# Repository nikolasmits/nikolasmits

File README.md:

<h1>Hi, I'm Nikolaos! <br/><a href="https://www.linkedin.com/in/nikolas-mitsokapas-6b18a51ba/">Electronic and Electrical Engineer</a>, <a href="https://www.linkedin.com/in/nikolas-mitsokapas-6b18a51ba/">Computer Science</a>

<h2>🤖 Control Systems and Robotics:</h2>

- <b>Automated Component Embedding Integration for an FDM 3D Printer</b>
  - [Modifying a TAZ 5 3D Printer with an end-effector gripper, toolchange mechanism & machine vision](https://github.com/nikolasmits/nikolasmits/tree/main/automated-component-embedding-integration-for-an-fdm-3d-printer)
- <b>Designing and Testing a a Maze Solving Robot</b>
  - [Four-wheeled robot with sensing and actuation for obstacle-based movement](https://github.com/nikolasmits/nikolasmits/tree/main/maze-solving-robot)
- <b>Braille-to-text-to-speech reading robot</b>
  - [UCL Neuphonic AI Hackathon](https://github.com/nikolasmits/nikolasmits/tree/main/braille-reading-robot)
- <b>Pick-and-place (PnP) Robot</b>
  - [Forward Kinematics, Inverse Kinematics & Trajectory planning of a PnP Robot](https://github.com/nikolasmits/nikolasmits/tree/main/pnp_robot)
- <b>Connected Bioreactor Control System</b>
  - [Remote monitoring and control of a small-scale bioreactor](https://github.com/nikolasmits/nikolasmits/tree/main/bioreactor-control-system)
- <b>Robotic Surgical Tool Design</b>
  - [Conformal tool design, surgical planning](https://github.com/nikolasmits/nikolasmits/tree/main/bioreactor-control-system)

<h2>👨‍💻 ML & DL Projects:</h2>

- <b>Sentiment Analysis (Deep Learning & Natural Language Processes)</b>
  - [Logistic Regression, Word2vec, LSTM & DistilBERT models](https://github.com/nikolasmits/nikolasmits/tree/main/sentiment-analysis)
- <b>Backpropagation in MLP, Transfer Learning in CNN and RL</b>
  - [Regression, Classification, Transfer Learning and Q-Learning](https://github.com/nikolasmits/nikolasmits/tree/main/backprop-mlp-transfer-learning-cnn-rl)
- <b>Image Procession</b>
  - [MATLAB Design for Image Processing](https://github.com/nikolasmits/nikolasmits/tree/main/image-processing)
- <b>Industrial Automation</b>
  - [Automated System for Deburring, Polishing and Storing car rims](https://github.com/nikolasmits/nikolasmits/tree/main/industrial-automation)

<h2> 🔌 Circuit Design and Hardware Development:</h2>

- <b>Smart Gym Wearable (Advanced Embedded Design for IoTSystems)</b>
  - [Embedded Systems, Schematic & PCB Design](https://github.com/nikolasmits/nikolasmits/tree/main/smart-gym-wearable)
- <b>Bio-signal Based Human Machine Interface (sEMG)</b>
  - [Schematic, PCB Design & Fabrication of an sEMG](https://github.com/nikolasmits/nikolasmits/tree/main/semg)
- <b>Digital Power Supply</b>
  - [Design & Fabrication of a DPS subsystem](https://github.com/nikolasmits/nikolasmits/tree/main/dps)

<h2> 🧠 Digital Design and Computer Architecture:</h2>

- <b>Design of a RISC-V central CPU</b>
  - [SystemVerilog description and Icarus Verilog simulation](https://github.com/nikolasmits/nikolasmits/tree/main/risc-v-central-cpu)
- <b>Audio descrambler</b>
  - [Design of digital audio descrambler](https://github.com/nikolasmits/nikolasmits/tree/main/audio-descrambler)

<h2> 📈 Simulation, Modelling and Technical Analysis:</h2>

- <b>Enhancement of Optical Absorption of Silicon Photovoltaics</b>
  - [Study of a hydrogenated amorphous silicion thin film PV cell with periodic gold nanowire gratings](https://github.com/nikolasmits/nikolasmits/tree/main/enhancement-of-optical-absorption-of-silicon-photovoltaics)
- <b>Digital transmitter, AWGN Communication channel & Digital Receiver</b>
  - [Design of a communication system](https://github.com/nikolasmits/nikolasmits/tree/main/comm-system)
- <b>Environmental Systems Mathematical Modelling</b>
  - [Simulating pollutant propagation across the Great Lakes](https://github.com/nikolasmits/nikolasmits/tree/main/environmental-systems-mathematical-modelling)
- <b>Mathematical model assessing the effects of altitude on the atmospheric pressure and density of air</b>
  - [MATLAB Mathematical model assessment](https://github.com/nikolasmits/nikolasmits/tree/main/mathematical-model-assessing-the-effects-of-altitude-on-the-atmospheric-pressure-and-density-of-air)
- <b>AIESEC Global Financial Case Competition</b>
  - [Financial performance and three-year projection](https://github.com/nikolasmits/nikolasmits/tree/main/aiesec-global-financial-case-competition)

<h2> 🤳 Connect with me:</h2>

[][linkedin]
[][email]

[email]: mailto:n.mitsokapas2003@gmail.com
[linkedin]: https://www.linkedin.com/in/nikolas-mitsokapas-6b18a51ba/

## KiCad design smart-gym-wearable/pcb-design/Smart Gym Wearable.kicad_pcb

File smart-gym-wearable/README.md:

# Smart Gym Wearable: Embedded Hardware and PCB Design

## Overview
This project involved the end-to-end hardware design of a **Smart Gym Wearable** intended to monitor workout motion and physiological state during exercise. The device combines:

- **motion sensing** using an ADXL343 3-axis accelerometer
- **heart-rate and pulse oximetry sensing** using the MAX30102
- **wireless communication** through an STM32WB55CEU6 with integrated Bluetooth Low Energy (BLE)
- **external flash memory** for extended data storage
- and a **battery-powered power management system** suitable for wearable use. 

The project covered the full hardware workflow from specification and component selection through schematic design, PCB layout, BOM preparation, and design-rule verification. :contentReference[oaicite:3]{index=3} :contentReference[oaicite:4]{index=4}

## Project Context
This project was completed for **ELEC0152: Advanced Embedded Design for IoT Systems – Circuit Design and Implementation**. The coursework required an academic-style hardware design report documenting the complete process of designing and implementing an electronic system, including:

- circuit specification
- refined component selection
- system block diagram
- full schematic
- PCB design
- and bill of materials analysis. :contentReference[oaicite:5]{index=5}

The workshop guidance also required:
- at least one sensor using **SPI, I2C, or UART**
- at least one actuator
- at least two protocols among **SPI, I2C, UART**
- **USB power and data**
- and **wireless communication**. :contentReference[oaicite:6]{index=6}

This wearable satisfies those requirements through:
- sensor interfacing over **I2C**
- external memory over **QSPI/SPI**
- USB connectivity
- BLE wireless communication
- and LED-based user feedback. :contentReference[oaicite:7]{index=7}

## My Contribution
This project appears to be an individual hardware design project, and the uploaded report is written in first person around your own design decisions. The work demonstrates my ability to take a product idea from system requirements to a manufacturable PCB implementation.

My contribution included:
- defining the wearable’s hardware objectives
- selecting and justifying the major ICs and support circuitry
- designing the full schematic
- creating the PCB layout in KiCad
- setting design rules and checking manufacturability
- compiling the BOM and supplier-linked part list
- and documenting the design trade-offs in a formal hardware report. :contentReference[oaicite:8]{index=8}

## Product Motivation
The report frames the wearable around a real user problem: while commercial devices such as fitness trackers and smartwatches provide high-level metrics, they often provide limited feedback on **exercise execution quality**, **repetition consistency**, or **training efficiency**. The device was therefore designed to support structured resistance training by monitoring movement and physiological state while transmitting raw data to a smartphone for higher-level analysis. :contentReference[oaicite:9]{index=9}

This gives the project a strong product-engineering angle rather than being only a component-integration exercise.

## System Architecture
The wearable is built around the **STM32WB55CEU6**, which was selected as the central MCU/SoC because it combines:
- microcontroller capability
- low-power operation
- and integrated **Bluetooth Low Energy** support,

making it well suited for a compact wearable design. :contentReference[oaicite:10]{index=10}

The main subsystems shown across the report and schematics are:
- motion sensing
- optical biometric sensing
- mixed-voltage I2C interfacing
- external flash memory
- battery charging and regulation
- USB connection
- and user input/output. :contentReference[oaicite:11]{index=11}

## Motion Sensing: ADXL343 Accelerometer
The design uses the **ADXL343**, a 3-axis digital MEMS accelerometer. According to its datasheet, it supports:
- selectable ranges up to **±16 g**
- digital output over **SPI or I2C**
- motion-related features such as activity, inactivity, tap, double-tap, and free-fall detection
- and low-power operation down to **23 µA**. :contentReference[oaicite:12]{index=12}

This makes it a good fit for workout tracking, where the device needs to capture both static orientation and dynamic motion while remaining power-efficient.

Your accelerometer schematic shows:
- **3.3 V supply**
- local decoupling capacitors
- interrupt lines
- and pull-up resistors for the I2C bus,

which indicates correct attention to practical digital sensor integration rather than just symbolic connection. The uploaded noise-vs-output-data-rate figure also shows awareness of the trade-off between bandwidth and noise in motion sensing, which is particularly relevant in movement analysis for exercise tracking. :contentReference[oaicite:13]{index=13}

## Biometric Sensing: MAX30102 Pulse Oximeter and Heart-Rate Sensor
The wearable uses the **MAX30102** for optical heart-rate and blood-oxygen sensing. The datasheet describes it as an integrated pulse oximeter and heart-rate monitor module designed specifically for **wearable devices**, with:
- internal LEDs
- photodetectors
- ambient-light rejection
- FIFO support
- and low-power operation. It operates with a **1.8 V logic supply** and a separate **3.3 V LED supply**. :contentReference[oaicite:14]{index=14}

That voltage requirement directly explains one of the more interesting design decisions in your schematic: the use of a **voltage-level translator** between the MCU side and the sensor side.

## Mixed-Voltage I2C and Level Translation
Because the MAX30102 uses a lower logic supply than the main 3.3 V MCU domain, the design includes the **PCA9306** dual bidirectional I2C voltage-level translator. According to the datasheet, the PCA9306 is intended for bidirectional translation of I2C/SMBus signals across voltage domains without the need for a direction pin, while requiring pull-up resistors on both sides of the bus. 

Your schematic reflects this correctly by placing the translator between the sensor-side and main I2C-side buses, with supporting pull-ups and enable handling. This is a strong design choice because it shows awareness of:
- logic-level compatibility
- bus integrity
- and safe integration of mixed-voltage peripherals in a wearable system. 

## Memory Expansion: External Flash
The design also includes **external QSPI flash memory** (`W25Q128JVS`) connected through dedicated flash control and IO lines. This is a strong systems decision because it extends local storage for raw sensor data beyond what would be practical using only internal MCU memory. The report explicitly mentions this as part of the design rationale for capturing workout data before or alongside wireless transfer. :contentReference[oaicite:17]{index=17}

Including both BLE transmission and local memory support makes the system much more realistic as a wearable platform.

## Power Management and Battery Charging
A key strength of the project is its complete power subsystem. The design includes:
- a **lithium-ion battery**
- the **MCP73832** charge-management IC
- and the **MIC5365-3.3** LDO regulator. 

The MCP73832 datasheet and your schematic indicate a simple Li-ion charging solution with charge programming through a resistor, while the MIC5365 provides a regulated **3.3 V rail** with:
- low dropout
- low quiescent current
- and strong PSRR,
which is highly suitable for battery-powered portable electronics. :contentReference[oaicite:18]{index=18}

This is particularly important in a mixed-signal wearable, where clean regulation benefits both the MCU and noise-sensitive sensors.

## User Interaction and Feedback
The design includes:
- a **pushbutton** for starting and ending workouts
- and LED indicators for workout state / user feedback. 

This satisfies the actuator requirement from the workshop guidance and also improves usability by giving the user a simple physical interaction point rather than requiring all control through software alone. :contentReference[oaicite:19]{index=19}

## PCB Design
The PCB work is one of the strongest parts of this project. The uploaded board views show:
- a compact rectangular form factor
- routed top and bottom copper
- dense mixed-signal placement
- dedicated sensor areas
- and an RF/antenna-aware layout region. 

The report also states that the PCB design process considered:
- RF constraints for the BLE antenna path
- component placement constraints
- grounding
- routing strategy
- and manufacturability. :contentReference[oaicite:20]{index=20}

The antenna datasheet you uploaded also suggests explicit attention to PCB antenna footprint and layout recommendations, which is an important sign of real embedded-RF design awareness rather than treating BLE as just a software feature. :contentReference[oaicite:21]{index=21}

## BOM and Component Selection
The BOM screenshots and component list show that the project did not stop at schematic completion. It includes:
- actual manufacturer part numbers
- footprints
- supplier / assembly information
- and availability checks.

The report and coursework brief both emphasise performance, availability, and cost trade-offs in component selection, and your uploaded stock screenshots support that this was actively considered for parts such as:
- MAX30102
- MCP73832
- and MIC5365. 

That makes this much closer to a real hardware design project than a purely academic schematic.

## Verification and Manufacturability
The uploaded screenshots show:
- **ERC with zero violations**
- **DRC with zero violations**
- and explicit PCB constraint settings for clearance, track width, annular rings, vias, and board-edge rules.

This is a very important portfolio point because it demonstrates that the PCB was not only drawn, but checked against practical manufacturability and consistency rules. In other words, the project reflects a design flow aimed at real fabrication rather than only conceptual layout.

## Why This Project Matters
What makes this project strong is that it combines several engineering domains in one device:

- embedded hardware design
- mixed-voltage digital interfacing
- low-power wearable sensing
- biometric and motion sensor integration
- battery charging and regulation
- BLE-ready embedded platform design
- memory expansion
- PCB layout and manufacturability

This is the kind of project that shows genuine readiness for embedded hardware, IoT, wearable technology, and PCB/system design roles.

## Engineering Skills Demonstrated
This project demonstrates skills in:
- **embedded hardware architecture**
- **wearable device design**
- **PCB design in KiCad**
- **sensor integration over I2C**
- **mixed-voltage interface design**
- **power management and Li-ion charging**
- **regulator selection and low-power design**
- **external flash integration**
- **BLE-aware PCB design**
- **design-rule verification**
- **BOM preparation and sourcing**
- **technical hardware reporting in academic/professional style**. 

## What I Learned
This project strengthened my understanding of how a complete embedded wearable is developed from the ground up. In particular, it showed me how important it is to think across the full hardware stack: product requirements, component compatibility, supply domains, bus protocols, signal integrity, battery management, PCB layout, and manufacturability all interact. It also reinforced that good hardware design is not only about making a circuit function, but about making it robust, power-efficient, buildable, and appropriate for the real application. 

## Repository Contents
- `README.md` – project summary
- `report/` – final hardware design report
- `pcb-design/` – KiCad project files
- `schematics-design/` – key schematic screenshots
- `images/` – PCB views, BOM, ERC/DRC, and component screenshots
- `datasheets/` – supporting technical references

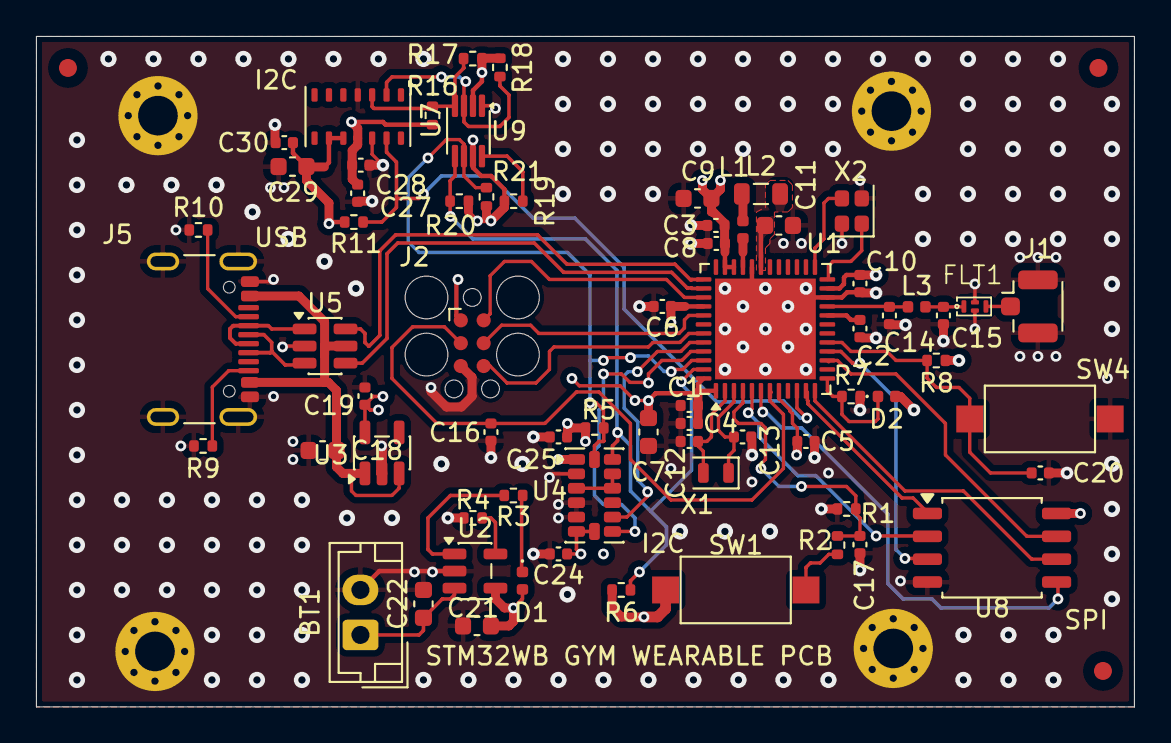
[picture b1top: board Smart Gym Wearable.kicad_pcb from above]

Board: 4 copper layers, 61.0 x 37.2 mm, 74 parts (0 on the bottom side), 47 nets.

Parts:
BT1: 4.2V; JST_EH_B2B-EH-A_1x02_P2.50mm_Vertical
C1, C2, C3, C4, C5, C6, C8, C10, C16, C17, C20: 100n; C_0402_1005Metric
C7, C9, C11, C18, C21, C22, C29: 4u7; C_0603_1608Metric
C12, C13: 10p; C_0402_1005Metric
C14: 0p8; C_0402_1005Metric
C15: 0p3; C_0402_1005Metric
C19: 4u7; C_0402_1005Metric
C24: 1u; C_0402_1005Metric
C25, C28, C30: 0u1; C_0402_1005Metric
C27: 10u; C_0402_1005Metric
D1, D2: LED; LED_0402_1005Metric
FID1, FID2, FID3: Fiducial; Fiducial_1mm_Mask2mm
FLT1: DLF162500LT-5028A1
H1, H2, H3, H4: MountingHole_Pad; MountingHole_2.2mm_M2_Pad_Via
J1: Conn_Coaxial; U.FL_Hirose_U.FL-R-SMT-1_Vertical
J2: TC2030; Tag-Connect_TC2030-IDC-FP_2x03_P1.27mm_Vertical
J5: USB_C_Receptacle_USB2.0_16P; USB_C_Receptacle_GCT_USB4105-xx-A_16P_TopMnt_Horizontal
L1: 10n; L_0402_1005Metric
L2: 10u; L_0805_2012Metric
L3: 2n7; L_0402_1005Metric
R1, R9, R10: 5k1; R_0402_1005Metric
R2: 100R; R_0402_1005Metric
R3, R7: 470R; R_0402_1005Metric
R4: 2k; R_0402_1005Metric
R5, R6: 4k7; R_0402_1005Metric
R8: 10k; R_0402_1005Metric
R11, R17, R18, R20, R21: 3k3; R_0402_1005Metric
R16: 1k; R_0402_1005Metric
R19: 200k; R_0402_1005Metric
SW1, SW4: SW_Push; SW_SPST_CK_RS282G05A3
U1: STM32WB55CEU6; QFN-48-1EP_7x7mm_P0.5mm_EP5.6x5.6mm
U2: MCP73832-2-OT; SOT-23-5
U3: MIC5365-3.3YD5; TSOT-23-5
U4: ADXL343; LGA-14_3x5mm_P0.8mm_LayoutBorder1x6y
U5: USBLC6-2SC6; SOT-23-6
U7: MAX30102; Maxim_OLGA-14_3.3x5.6mm_P0.8mm
U8: W25Q128JVS; SOIC-8_5.3x5.3mm_P1.27mm
U9: PCA9306DC1; VSSOP-8_2.3x2mm_P0.5mm
X1: 32kHz768; Crystal_SMD_2012-2Pin_2.0x1.2mm
X2: 32MHz; Crystal_SMD_2016-4Pin_2.0x1.6mm

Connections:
+1V8: C27.1, C28.1, R16.1, U7.11 (VDD)
+3.3V: C1.1, C2.1, C3.1, C4.1, C5.1, C6.1, C7.1, C8.1, C9.1, C10.1, C19.1, C24.1, C25.1, C29.1, C30.1, D2.2 (A), J2.1 (VCC), R5.1, R6.1, R8.2, R11.2, R17.2, R18.2, R19.2, R20.2, R21.2, SW1.2, U1.1 (VBAT), U1.8 (VDDA), U1.20 (VDD), U1.23 (VDDRF), U1.34 (VDDSMPS), U1.35 (VDD), U1.40 (VDDUSB), U1.48 (VDD), U3.5 (VOUT), U4.1 (Vdd_I/O), U4.6 (Vs), U4.7 (~CS), U7.9 (VLED+), U7.10 (VLED+), U8.8 (VCC), U9.2 (VREF1), U9.7 (VREF2)
+5V: C18.1, C21.1, D1.2 (A), J5.A4 (VBUS), J5.A9 (VBUS), J5.B4 (VBUS), J5.B9 (VBUS), U2.4 (V_{DD}), U3.1 (VIN), U3.3 (EN), U5.5 (VBUS)
/STM32 base circuit/BOOT0: C17.1, R1.1, R2.1, U1.4 (PH3)
/STM32 base circuit/HSE_IN: U1.25 (OSC_IN), X2.3
/STM32 base circuit/HSE_OUT: U1.24 (OSC_OUT), X2.1
/STM32 base circuit/LSE_IN: C12.1, U1.2 (PC14), X1.2
/STM32 base circuit/LSE_OUT: C13.1, U1.3 (PC15), X1.1
/STM32 base circuit/RF: C14.1, L3.1, U1.21 (RF1)
/STM32 base circuit/RF_ANT: FLT1.3 (OUT), J1.1 (In)
/STM32 base circuit/RF_MATCH: C15.1, FLT1.1 (IN), L3.2
/STM32 base circuit/SMPSFB: C11.1, L2.2, U1.31 (VFBSMPS)
/STM32 base circuit/SMPSLX: L1.1, U1.33 (VLXSMPS)
/STM32 base circuit/SMPSLXL: L1.2, L2.1
/STM32 base circuit/SWD_CLK: J2.4 (SWCLK), U1.41 (PA14)
/STM32 base circuit/SWD_DIO: J2.2 (SWDIO), U1.39 (PA13)
/STM32 base circuit/SWD_TRC: J2.6 (SWO), U1.43 (PB3)
/USB/USBC_D+: J5.A6 (D+), J5.B6 (D+), U5.3 (I/O2)
/USB/USBC_D-: J5.A7 (D-), J5.B7 (D-), U5.1 (I/O1)
/USB/USB_CC1: J5.A5 (CC1), R10.1
/USB/USB_CC2: J5.B5 (CC2), R9.1
FLASH_CLK: U1.12 (PA3), U8.6 (CLK)
FLASH_CS: U1.11 (PA2), U8.1 (~CS)
GND: BT1.2 (-), C1.2, C2.2, C3.2, C4.2, C5.2, C6.2, C7.2, C8.2, C9.2, C10.2, C11.2, C12.2, C13.2, C14.2, C15.2, C16.2, C17.2, C18.2, C19.2, C20.2, C21.2, C22.2, C24.2, C25.2, C27.2, C28.2, C29.2, C30.2, FLT1.2 (GND), FLT1.4 (GND), H1.1, H2.1, H3.1, H4.1, J1.2 (Ext), J2.5 (GND), J5.A1 (GND), J5.A12 (GND), J5.B1 (GND), J5.B12 (GND), J5.S1 (SHIELD), R1.2, R4.2, R7.2, R9.2, R10.2, SW4.2, U1.22 (VSSRF), U1.32 (VSSSMPS), U1.49 (VSS), U2.2 (V_{SS}), U3.2 (GND), U4.2 (GND), U4.4 (GND), U4.5 (GND), U5.2 (GND), U7.4 (PGND), U7.12 (GND), U8.4 (GND), U9.1 (GND), X2.2, X2.4
I2C_SCL2: R5.2, R21.1, U1.46 (PB6), U4.14 (SCL/SCLK), U9.6 (SCL2)
I2C_SDA2: R6.2, R20.1, U1.47 (PB7), U4.13 (SDA/SDI/SDIO), U9.5 (SDA2)
INT1_ADXL343_PB5: U1.45 (PB5), U4.8 (INT1)
INT2_ADXL343_PB4: U1.44 (PB4), U4.9 (INT2)
MAX30102_INT: R11.1, U1.10 (PA1), U7.13 (~INT)
unnamed: BT1.1 (+), C22.1, U2.3 (V_{BAT})
unnamed: D1.1 (K), R3.1
unnamed: R2.2, SW1.1
unnamed: R4.1, U2.5 (PROG)
unnamed: R3.2, U2.1 (STAT)
unnamed: U4.3 (RES), U4.11 (RES), U4.12 (SDO/ADDR)
unnamed: R18.1, U7.2 (SCL), U9.3 (SCL1)
unnamed: R16.2, R17.1, U7.3 (SDA), U9.4 (SDA1)
unnamed: R19.1, U9.8 (EN)
QUADSPI_BK1_IO0: U1.6 (PB9), U8.5 (DI/IO_{0})
QUADSPI_BK1_IO1: U1.5 (PB8), U8.2 (DO/IO_{1})
QUADSPI_BK1_IO2: U1.16 (PA7), U8.3 (~WP/IO_{2})
QUADSPI_BK1_IO3: U1.15 (PA6), U8.7 (~HOLD/~RESET/IO_{3})
START_END_WORKOUT: C20.1, R8.1, SW4.1, U1.17 (PA8)
SWD_NRST: C16.1, J2.3 (~RESET), U1.7 (NRST)
USB_D+: U1.38 (PA12), U5.4 (I/O2)
USB_D-: U1.37 (PA11), U5.6 (I/O1)
Workout_LED: D2.1 (K), R7.1, U1.13 (PA4)

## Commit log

2026-04-06 Update README
    Added email contact information and removed placeholder text.
2026-04-06 Add example section to README.md
2026-04-07 Fix heading format and update project listings
    Corrected heading format and added project details under Circuit Design and Hardware Development.
2026-04-07 Updated README
    Updated project sections and improved formatting in README.
2026-04-07 Fix GitHub link to point to LinkedIn profile
    Updated the GitHub link in the README to point to the LinkedIn profile.
2026-04-07 Enhance README with detailed project documentation
    Expanded the README to include project overview, contributions, technical work, results, skills demonstrated, tools, and lessons learned.
2026-04-07 Remove placeholder.txt file
2026-04-07 Delete unused placeholder.txt file
    Remove placeholder file as it is no longer needed.
2026-04-07 Enhance README with project details and contributions
    Added detailed project overview, context, contributions, and key engineering skills demonstrated in the README.
2026-04-07 Expand README with comprehensive project details
    Added detailed project overview, context, contributions, problem definition, sensing strategy, actuation design, navigation logic, Arduino implementation, engineering skills, and learning outcomes.
2026-04-07 Update README to remove 'brief/' directory reference
    Removed mention of 'brief/' directory from repository contents.
2026-04-07 Expand README with project details and contributions
    Added detailed project overview, context, contributions, and engineering skills demonstrated in the industrial automation of wheel retrieval, deburring, polishing, and storage.
2026-04-07 Update README with project details and contributions
    Added detailed project overview, context, contributions, and engineering skills demonstrated for the Smart Gym Wearable.
2026-04-07 Rename alexnet_adam_accuracy.png to backprop-mlp-transfer-learning-cnn-rl/task_3/alexnet_adam_accuracy.png
2026-04-07 Rename alexnet_adam_performance.png to backprop-mlp-transfer-learning-cnn-rl/task_3/alexnet_adam_performance.png
2026-04-07 Rename alexnet_parameter_tuning_results.csv to backprop-mlp-transfer-learning-cnn-rl/task_3/alexnet_parameter_tuning_results.csv
2026-04-07 Rename alexnet_sgd_performance.png to backprop-mlp-transfer-learning-cnn-rl/task_3/alexnet_sgd_performance.png
2026-04-07 Rename alexnet_sgd_accuracy.png to backprop-mlp-transfer-learning-cnn-rl/task_3/alexnet_sgd_accuracy.png
2026-04-07 Rename googlenet_adam_accuracy.png to backprop-mlp-transfer-learning-cnn-rl/task_3/googlenet_adam_accuracy.png
2026-04-07 Rename googlenet_adam_performance.png to backprop-mlp-transfer-learning-cnn-rl/task_3/googlenet_adam_performance.png
2026-04-07 Rename googlenet_confusion_matrix.png to backprop-mlp-transfer-learning-cnn-rl/task_3/googlenet_confusion_matrix.png
2026-04-07 Rename googlenet_fruits.pth to backprop-mlp-transfer-learning-cnn-rl/task_3/googlenet_fruits.pth
2026-04-07 Rename googlenet_parameter_tuning_results.csv to backprop-mlp-transfer-learning-cnn-rl/task_3/googlenet_parameter_tuning_results.csv
2026-04-07 Rename googlenet_sgd_accuracy.png to backprop-mlp-transfer-learning-cnn-rl/task_3/googlenet_sgd_accuracy.png
2026-04-07 Rename googlenet_sgd_performance.png to backprop-mlp-transfer-learning-cnn-rl/task_3/googlenet_sgd_performance.png
2026-04-07 Rename task_3_b.ipynb to backprop-mlp-transfer-learning-cnn-rl/task_3/task_3_b.ipynb
2026-04-07 Rename task_3_c.ipynb to backprop-mlp-transfer-learning-cnn-rl/task_3/task_3_c.ipynb
2026-04-07 Rename task_3_d_alexnet.ipynb to backprop-mlp-transfer-learning-cnn-rl/task_3/task_3_d_alexnet.ipynb
2026-04-07 Rename task_3_d_googlenet.ipynb to backprop-mlp-transfer-learning-cnn-rl/task_3/task_3_d_googlenet.ipynb
2026-04-07 Rename task_3_model_graphs.py to backprop-mlp-transfer-learning-cnn-rl/task_3/task_3_model_graphs.py
2026-04-08 Create robotic-surgical-tool
2026-04-08 Remove robotic-surgical-tool file
2026-05-06 Create Report
2026-05-06 Remove empty Report file
2026-05-06 Rename README.md to placeholder.txt
2026-05-06 Update Report
2026-05-06 Add machine vision implementation for image classification
    Implement machine vision code for classifying images as 'Success' or 'Fail' based on a trained model. Includes dataset loading, model building, training, and evaluation functionalities.
2026-05-06 Implement embedded component extraction from 3MF
    This code extracts embedded components from a 3MF CAD file, computes their bounding boxes, and saves the updated model along with performance metrics.
2026-05-06 Add G-code streaming implementation for embedding
    Implement G-code streaming for embedding components in 3D printing. This includes functions for loading component geometry, extracting layer height, connecting to the printer, and sending G-code comm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
2026-05-06 Add End-effector Arduino control code
2026-05-06 Update README to streamline repository contents
    Consolidate descriptions of 'code' and 'images' directories in README.
2026-05-06 Enhance README with project overview and model details
    Expanded the README to provide a comprehensive overview of the sentiment classification project, detailing models, methodologies, results, and contributions.
2026-05-06 Rename sentiment-analysis/code/sentiment_analysis_code.txt to sentiment-analysis/code/models/placeholder.txt
2026-05-06 Add placeholder.txt to sentiment-analysis/code
2026-05-06 Add logistic_model.py for sentiment analysis
2026-05-06 Implement evaluation utilities for model metrics
    Added evaluation utilities for model performance metrics including accuracy, F1 score, and ROC-AUC. Also implements saving confusion matrix plots to disk.
2026-05-06 Implement sentiment classification pipeline in main.py
    This script serves as the main entry point for the sentiment classification pipeline, executing the loading of data, training of models, evaluation, and saving of results.
